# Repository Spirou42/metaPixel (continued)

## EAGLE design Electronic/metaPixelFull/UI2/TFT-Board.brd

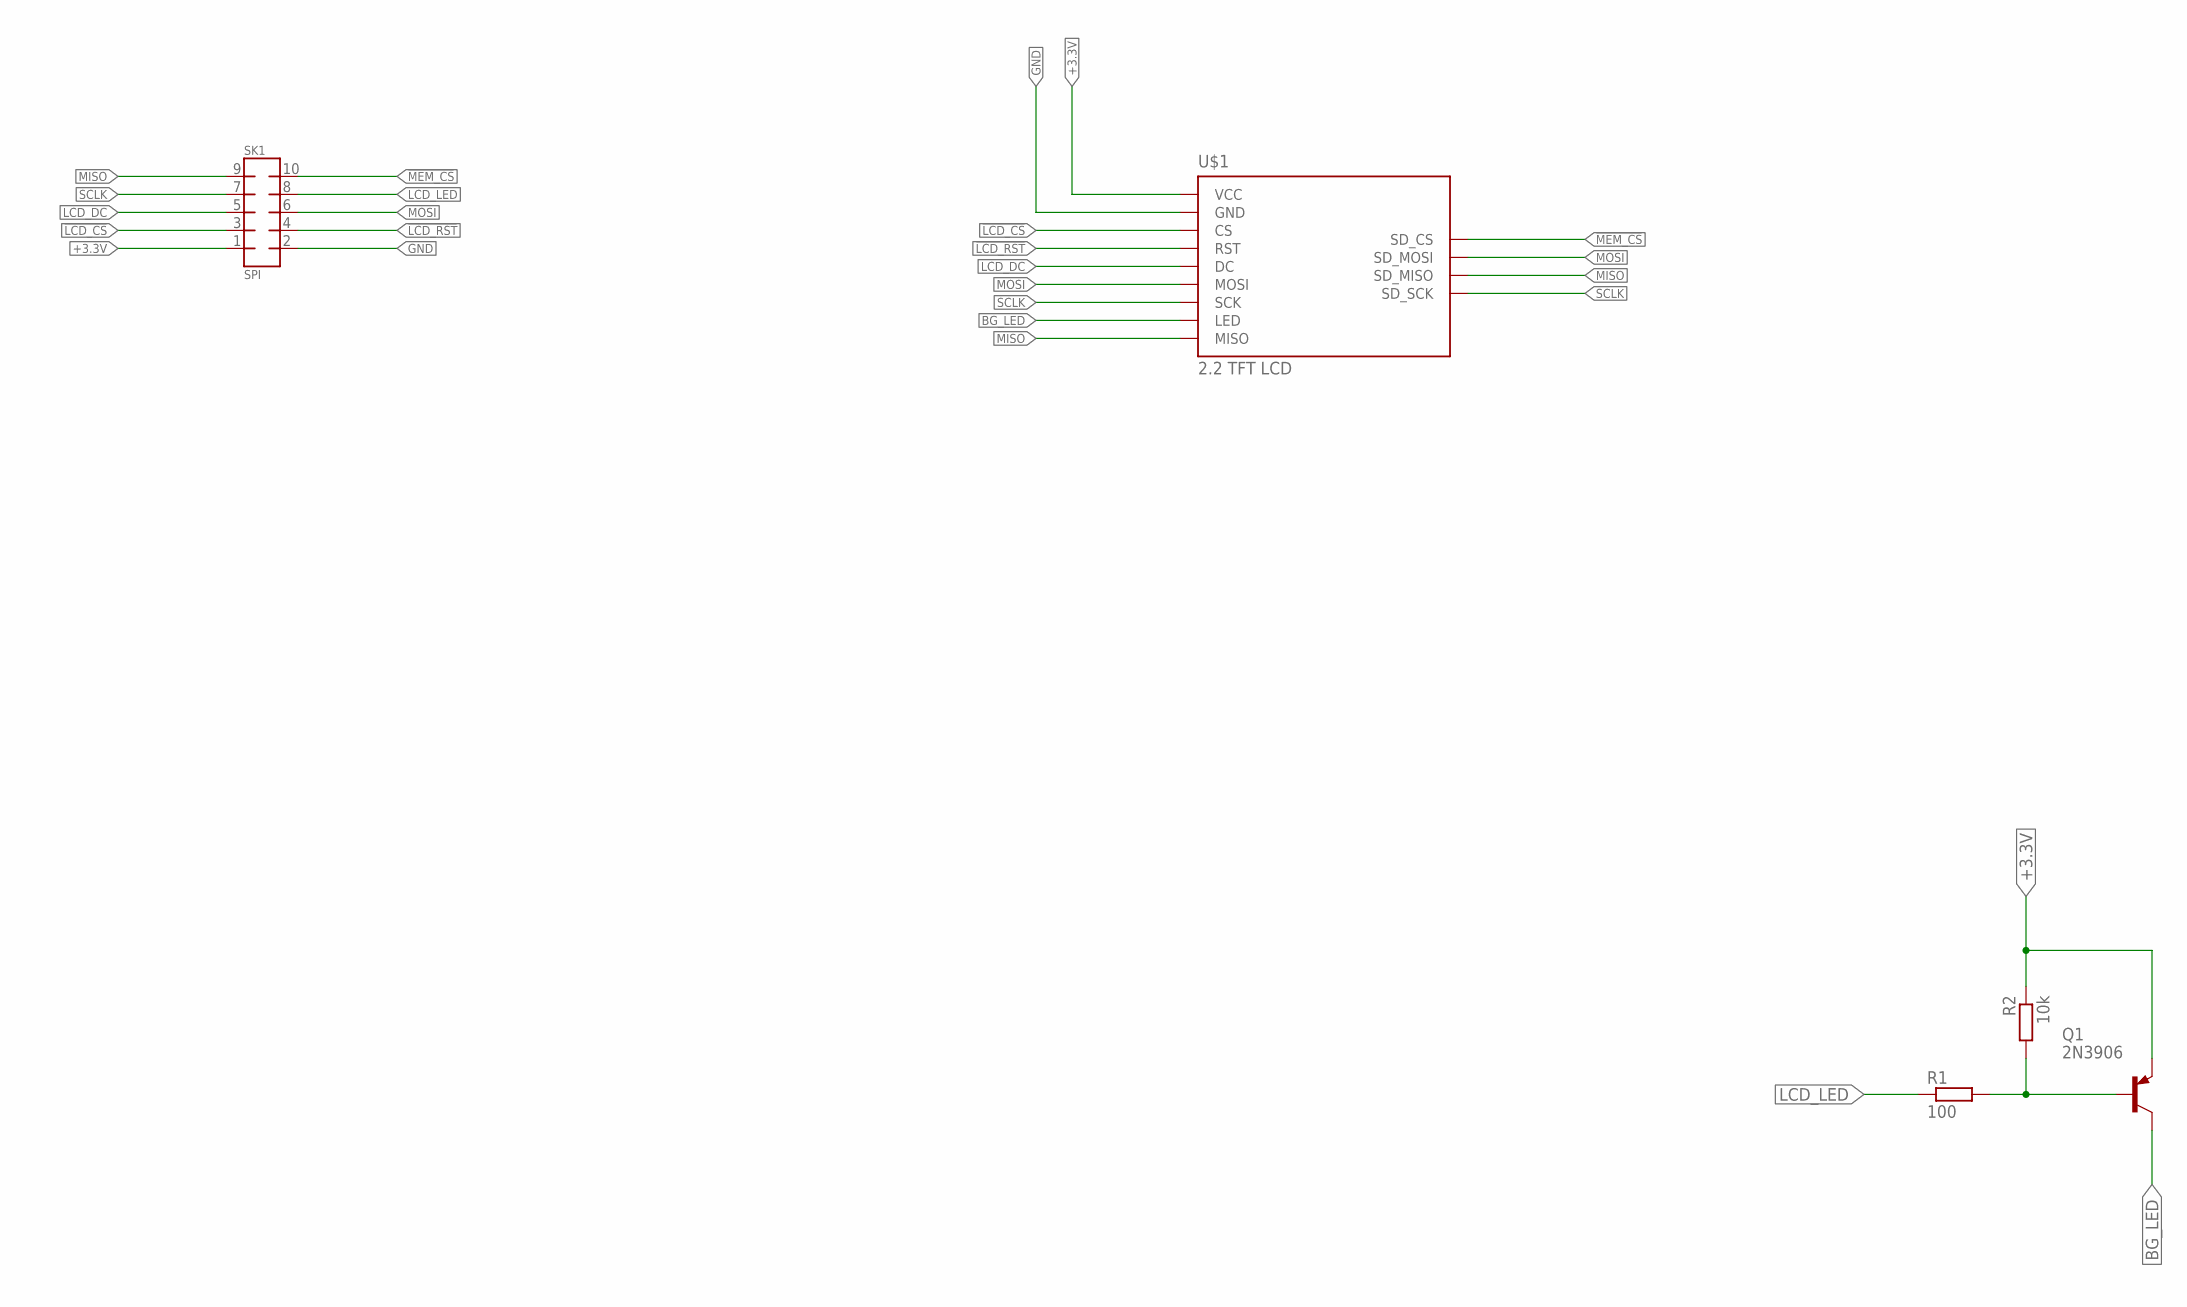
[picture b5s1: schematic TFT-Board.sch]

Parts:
Q1: 2N3906; TO92
R1: 100; 0204/7
R2: 10k; 0204/7
SK1: SPI; AMP-215079-10
U$1: 2.2_TFT_LCDNEW; 2.2_TFT_LCD_LEDSEE

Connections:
!LCD_CS: SK1.3, U$1.P$3_CS (CS)
!LCD_RST: SK1.4, U$1.P$2_RESET (RST)
!MEM_CS: SK1.10, U$1.P$2_SD_CS (SD_CS)
+3.3V: Q1.3 (E), R2.1, SK1.1, U$1.P$5_VCC (VCC)
BG_LED: Q1.1 (C), U$1.P$8_LED (LED)
GND: SK1.2, U$1.P$4_GND (GND)
LCD_DC: SK1.5, U$1.P$1_DC (DC)
LCD_LED: R1.1, SK1.8
MISO: SK1.9, U$1.P$3_SD_MISO (SD_MISO), U$1.P$9_MISO (MISO)
MOSI: SK1.6, U$1.P$1_SD_MOSI (SD_MOSI), U$1.P$6_MOSI (MOSI)
unnamed: Q1.2 (B), R1.2, R2.2
SCLK: SK1.7, U$1.P$4_SD_SCK (SD_SCK), U$1.P$7_SCK (SCK)

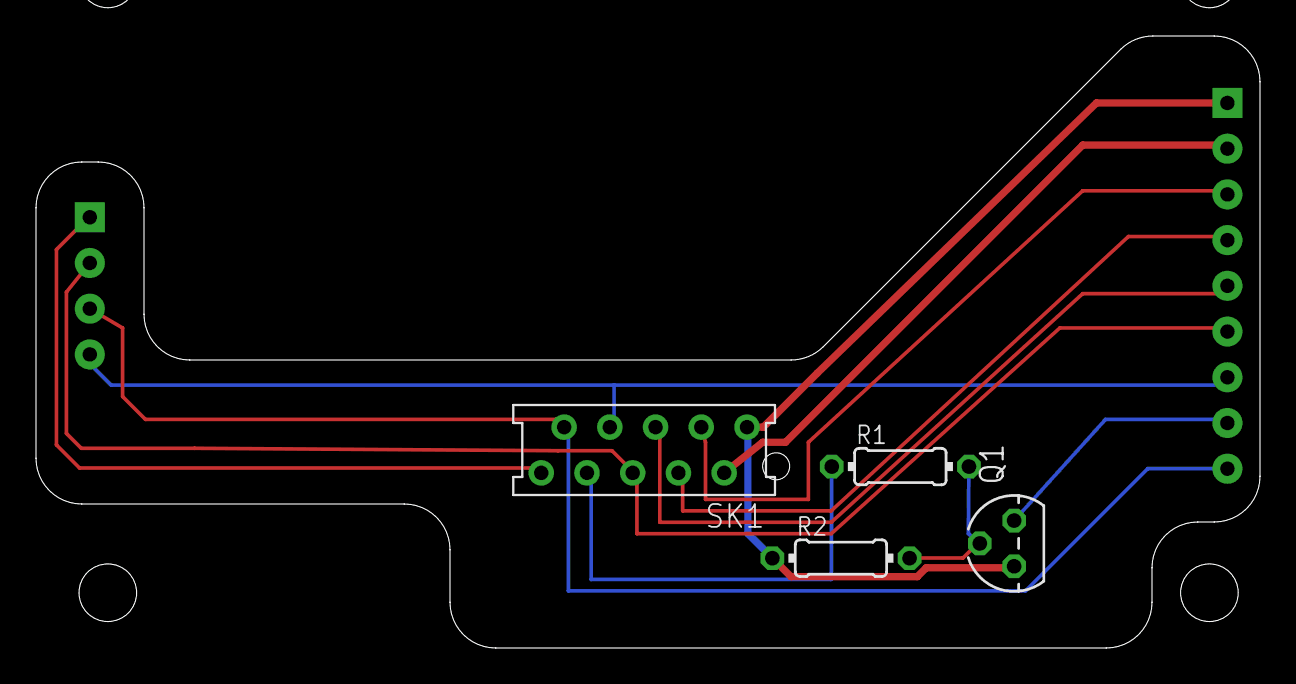
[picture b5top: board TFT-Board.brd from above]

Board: 2 copper layers, 68.0 x 34.0 mm, 5 parts (1 on the bottom side), 12 nets.

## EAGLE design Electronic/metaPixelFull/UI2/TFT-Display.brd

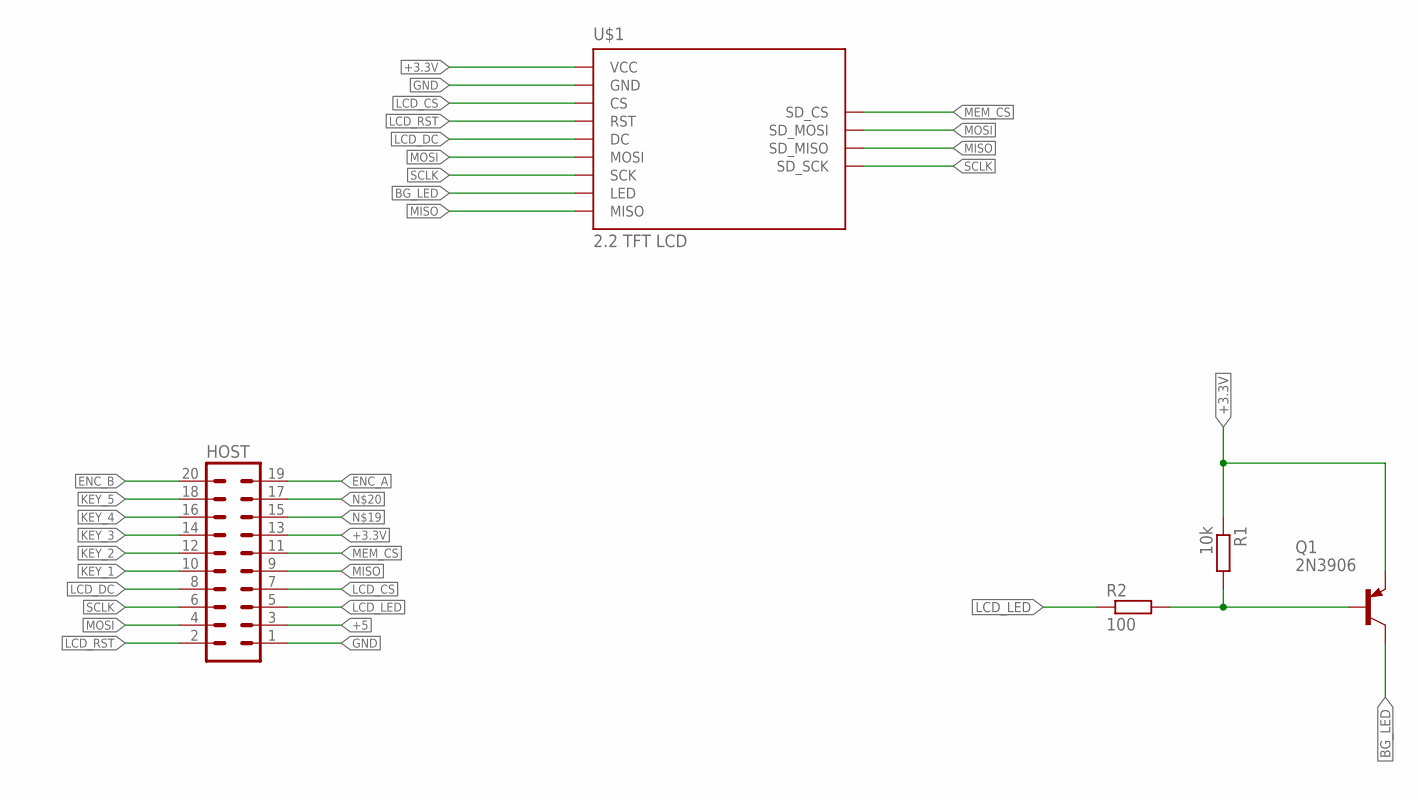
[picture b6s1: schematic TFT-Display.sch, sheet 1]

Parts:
HOST: ML20L
Q1: 2N3906; TO92
R1: 10k; 0204/7
R2: 100; 0204/7
U$1: 2.2_TFT_LCDNEW; 2.2_TFT_LCD_LEDSEE

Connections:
!LCD_CS: HOST.7, U$1.P$3_CS (CS)
!LCD_RST: HOST.2, U$1.P$2_RESET (RST)
!MEM_CS: HOST.11, U$1.P$2_SD_CS (SD_CS)
+3.3V: HOST.13, Q1.3 (E), R1.1, U$1.P$5_VCC (VCC); also elsewhere on the board
+5: HOST.3
BG_LED: Q1.1 (C), U$1.P$8_LED (LED)
ENC_A: HOST.19; also elsewhere on the board
ENC_B: HOST.20; also elsewhere on the board
GND: HOST.1, U$1.P$4_GND (GND); also elsewhere on the board
KEY_1: HOST.10; also elsewhere on the board
KEY_2: HOST.12; also elsewhere on the board
KEY_3: HOST.14; also elsewhere on the board
KEY_4: HOST.16; also elsewhere on the board
KEY_5: HOST.18; also elsewhere on the board
LCD_DC: HOST.8, U$1.P$1_DC (DC)
LCD_LED: HOST.5, R2.1
MISO: HOST.9, U$1.P$3_SD_MISO (SD_MISO), U$1.P$9_MISO (MISO)
MOSI: HOST.4, U$1.P$1_SD_MOSI (SD_MOSI), U$1.P$6_MOSI (MOSI)
unnamed: Q1.2 (B), R1.2, R2.2
SCLK: HOST.6, U$1.P$4_SD_SCK (SD_SCK), U$1.P$7_SCK (SCK)

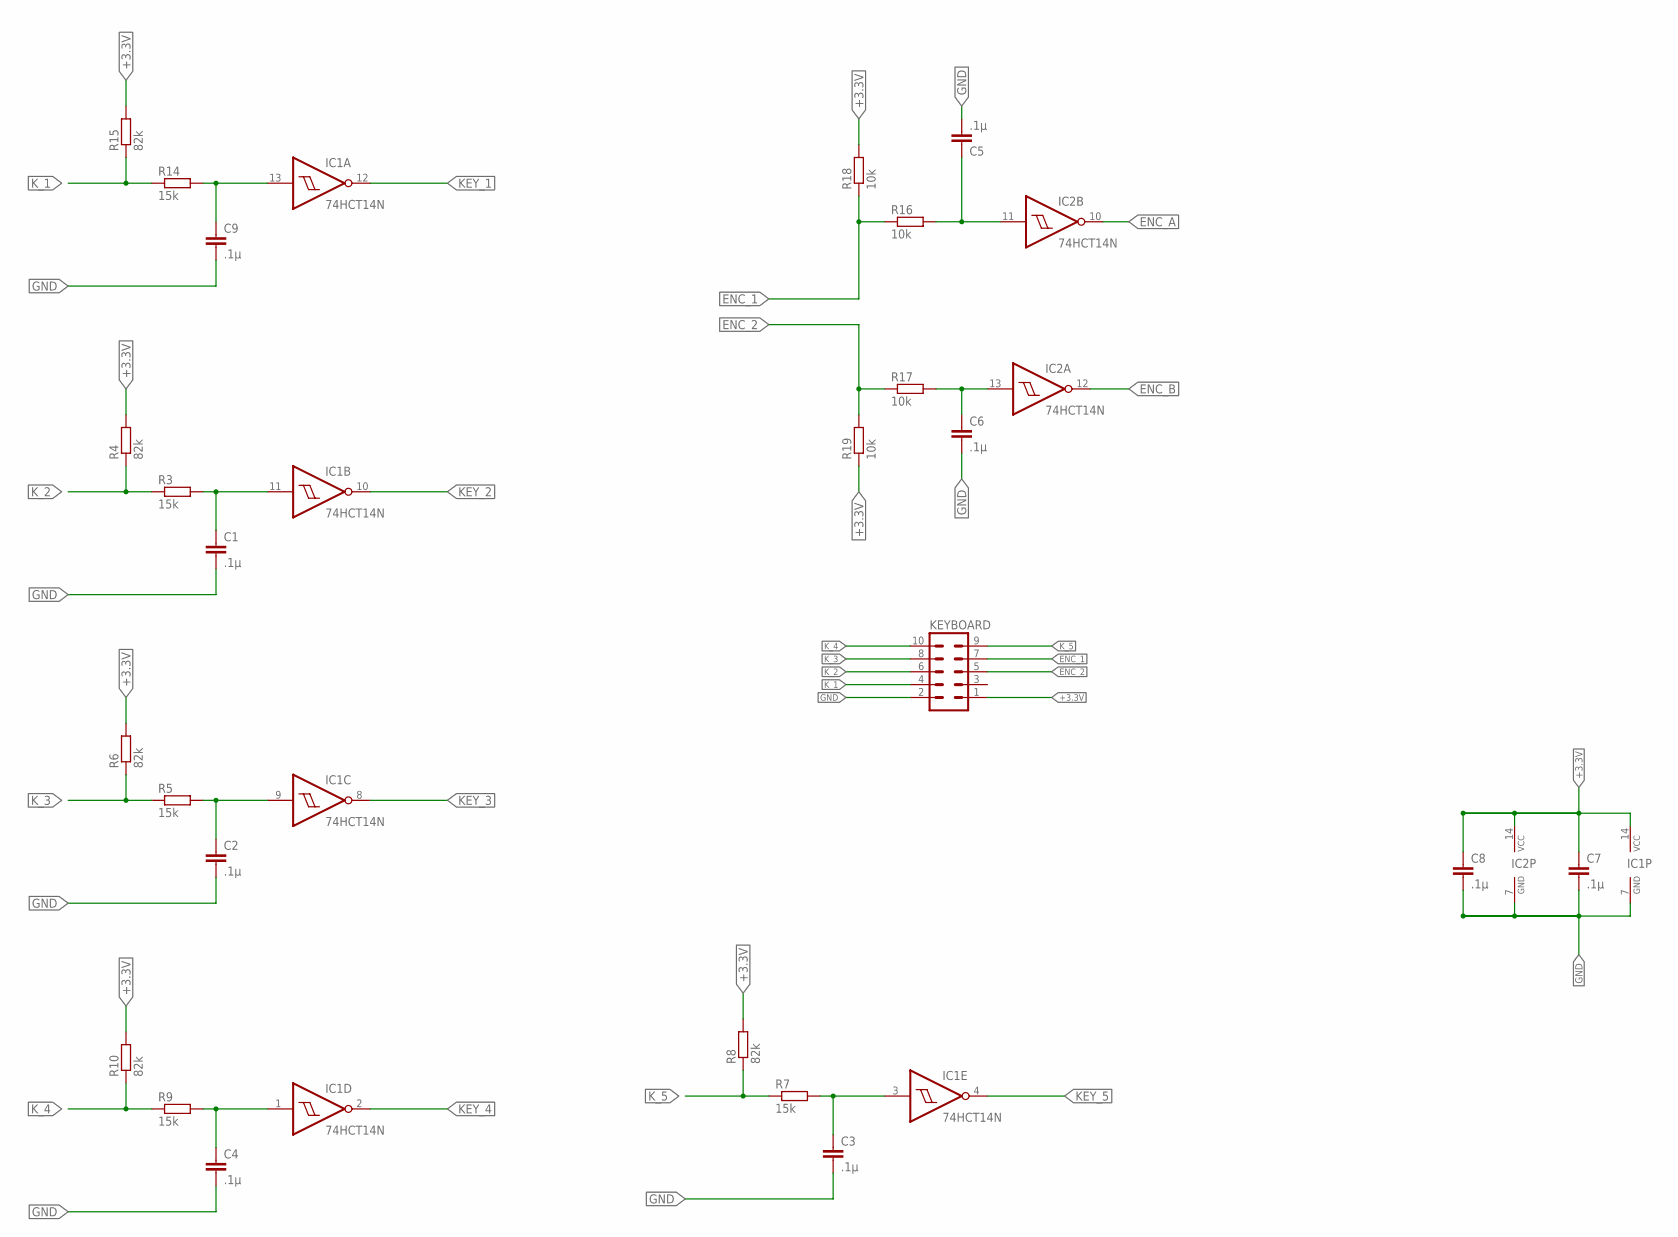
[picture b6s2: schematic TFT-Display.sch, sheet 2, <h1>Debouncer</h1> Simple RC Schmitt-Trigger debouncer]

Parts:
C1, C2, C3, C4, C5, C6, C7, C8, C9: .1µ; C025-024X044
IC1, IC2: 74HCT14N; DIL14
KEYBOARD: ML10L
R3, R5, R7, R9, R14: 15k; 0204/7
R4, R6, R8, R10, R15: 82k; 0204/7
R16, R17, R18, R19: 10k; 0204/7

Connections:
+3.3V: C7.1, C8.1, IC1.14 (VCC), IC2.14 (VCC), KEYBOARD.1, R4.2, R6.2, R8.2, R10.2, R15.2, R18.2, R19.1; also elsewhere on the board
ENC1: C5.1, IC2.11 (I), R16.2
ENC2: C6.1, IC2.13 (I), R17.2
ENC_1: KEYBOARD.7, R16.1, R18.1
ENC_2: KEYBOARD.5, R17.1, R19.2
ENC_A: IC2.10 (O); also elsewhere on the board
ENC_B: IC2.12 (O); also elsewhere on the board
GND: C1.2, C2.2, C3.2, C4.2, C5.2, C6.2, C7.2, C8.2, C9.2, IC1.7 (GND), IC2.7 (GND), KEYBOARD.2; also elsewhere on the board
K1: C9.1, IC1.13 (I), R14.2
K2: C1.1, IC1.11 (I), R3.2
K3: C2.1, IC1.9 (I), R5.2
K4: C3.1, IC1.3 (I), R7.2
K5: C4.1, IC1.1 (I), R9.2
KEY_1: IC1.12 (O); also elsewhere on the board
KEY_2: IC1.10 (O); also elsewhere on the board
KEY_3: IC1.8 (O); also elsewhere on the board
KEY_4: IC1.2 (O); also elsewhere on the board
KEY_5: IC1.4 (O); also elsewhere on the board
K_1: KEYBOARD.4, R14.1, R15.1
K_2: KEYBOARD.6, R3.1, R4.1
K_3: KEYBOARD.8, R5.1, R6.1
K_4: KEYBOARD.10, R9.1, R10.1
K_5: KEYBOARD.9, R7.1, R8.1

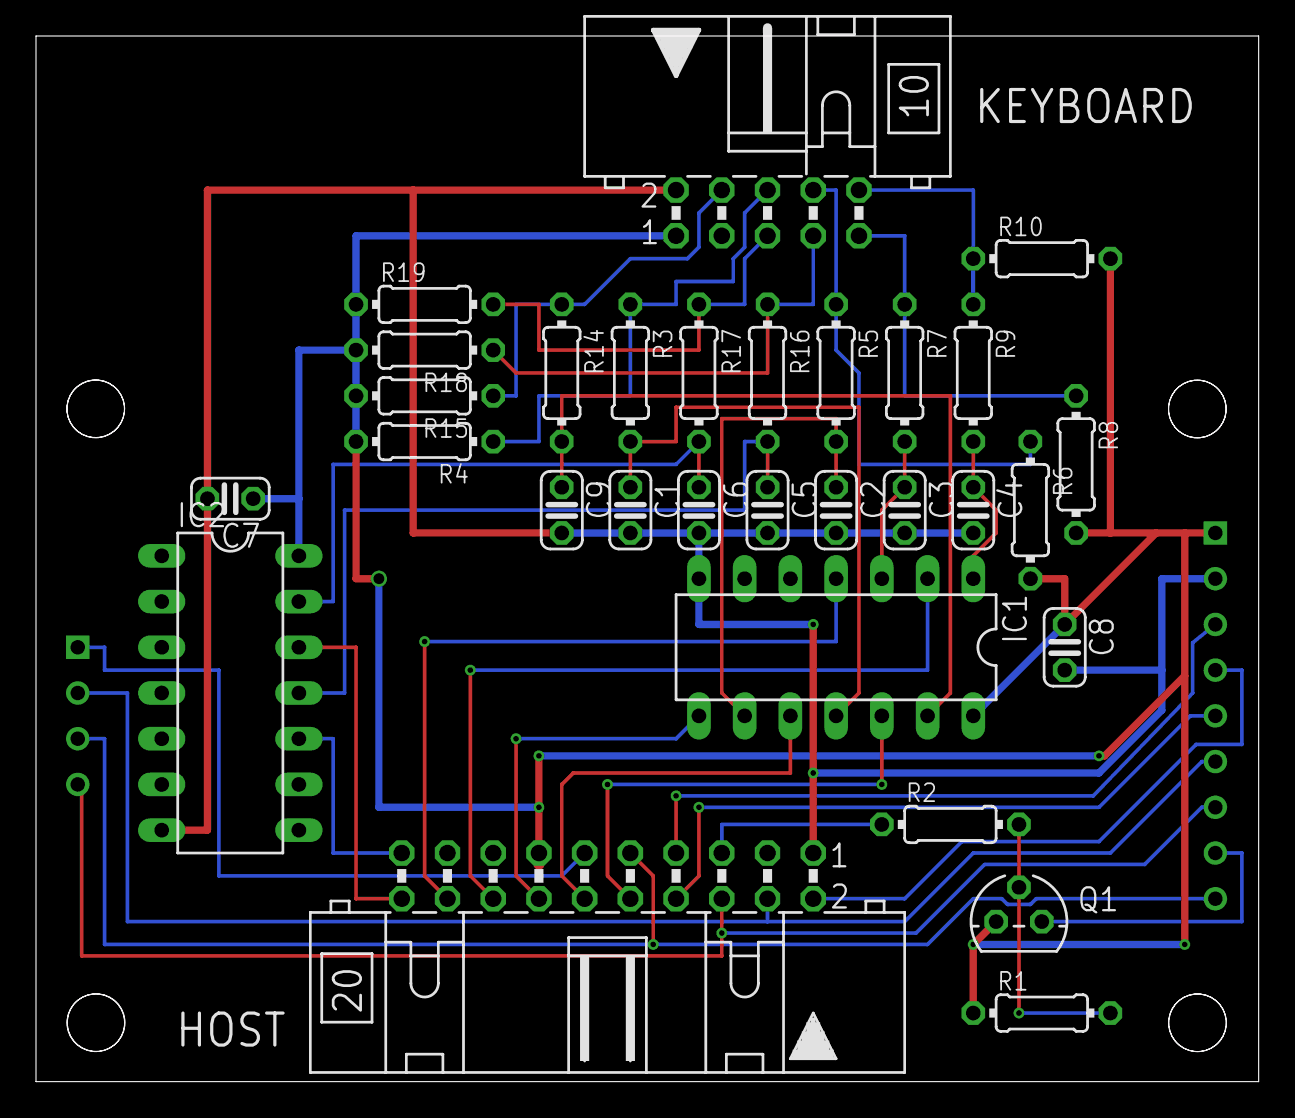
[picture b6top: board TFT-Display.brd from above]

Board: 2 copper layers, 67.9 x 58.1 mm, 31 parts (1 on the bottom side), 33 nets.

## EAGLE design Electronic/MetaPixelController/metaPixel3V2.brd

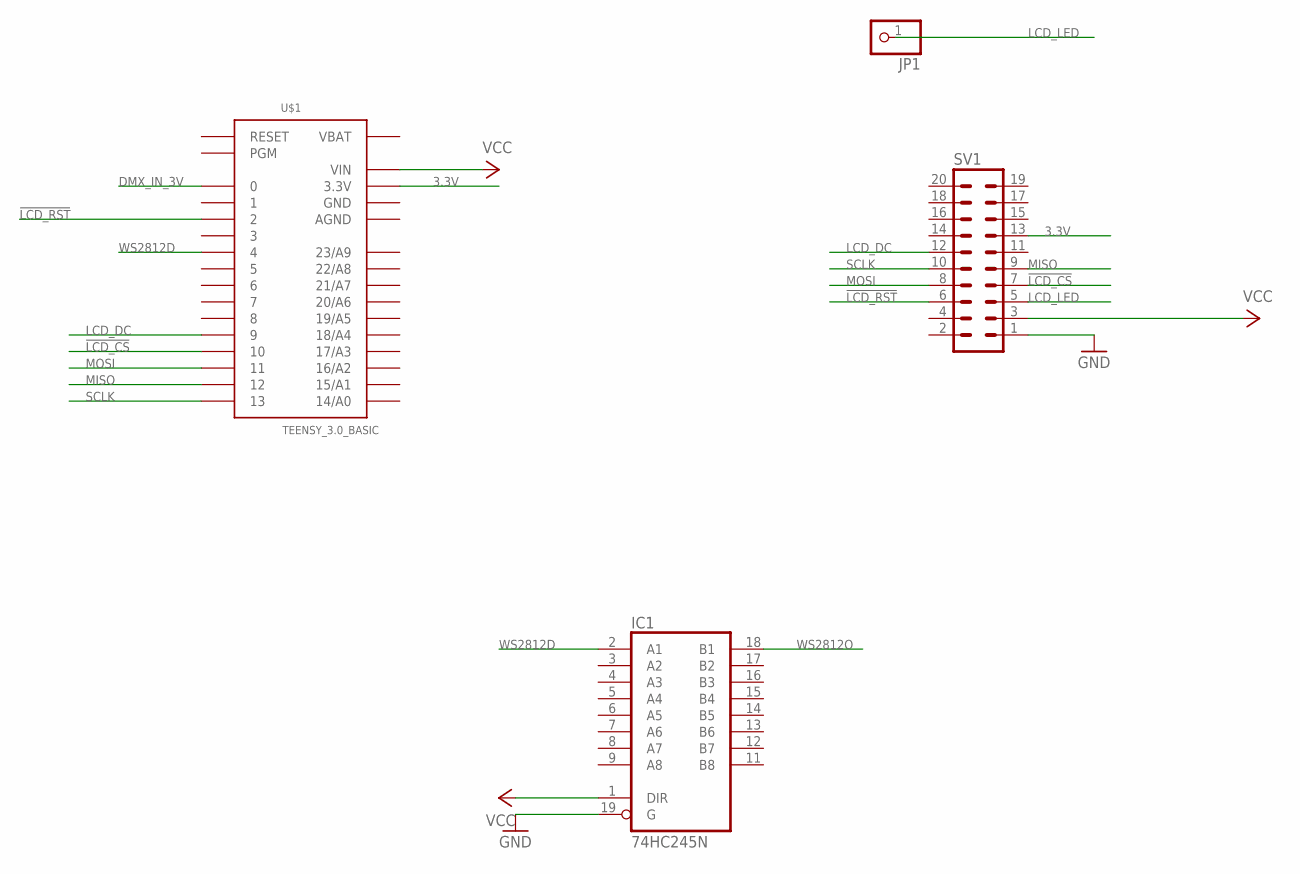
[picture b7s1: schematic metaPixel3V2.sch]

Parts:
IC1: 74HC245N; DIL20
JP1: PINHD-1X1; 1X01
SV1: ML20
U$1: TEENSY_3.0_BASIC

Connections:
3.3V: SV1.13, U$1.3.3V, U$1.3.3V1 (3.3V)
!LCD_CS: SV1.7, U$1.10
!LCD_RST: SV1.6, U$1.2
AGND: U$1.AGND
DMX_IN_3V: U$1.0
GND: IC1.10 (GND), IC1.19 (G), SV1.1, U$1.GND, U$1.GND1 (GND)
LCD_DC: SV1.12, U$1.9
LCD_LED: JP1.1, SV1.5
MISO: SV1.9, U$1.12
MOSI: SV1.8, U$1.11
SCLK: SV1.10, U$1.13
VBAT: U$1.VBAT
VCC: IC1.1 (DIR), IC1.20 (VCC), SV1.3, U$1.VIN
WS2812D: IC1.2 (A1), U$1.4
WS2812O: IC1.18 (B1)

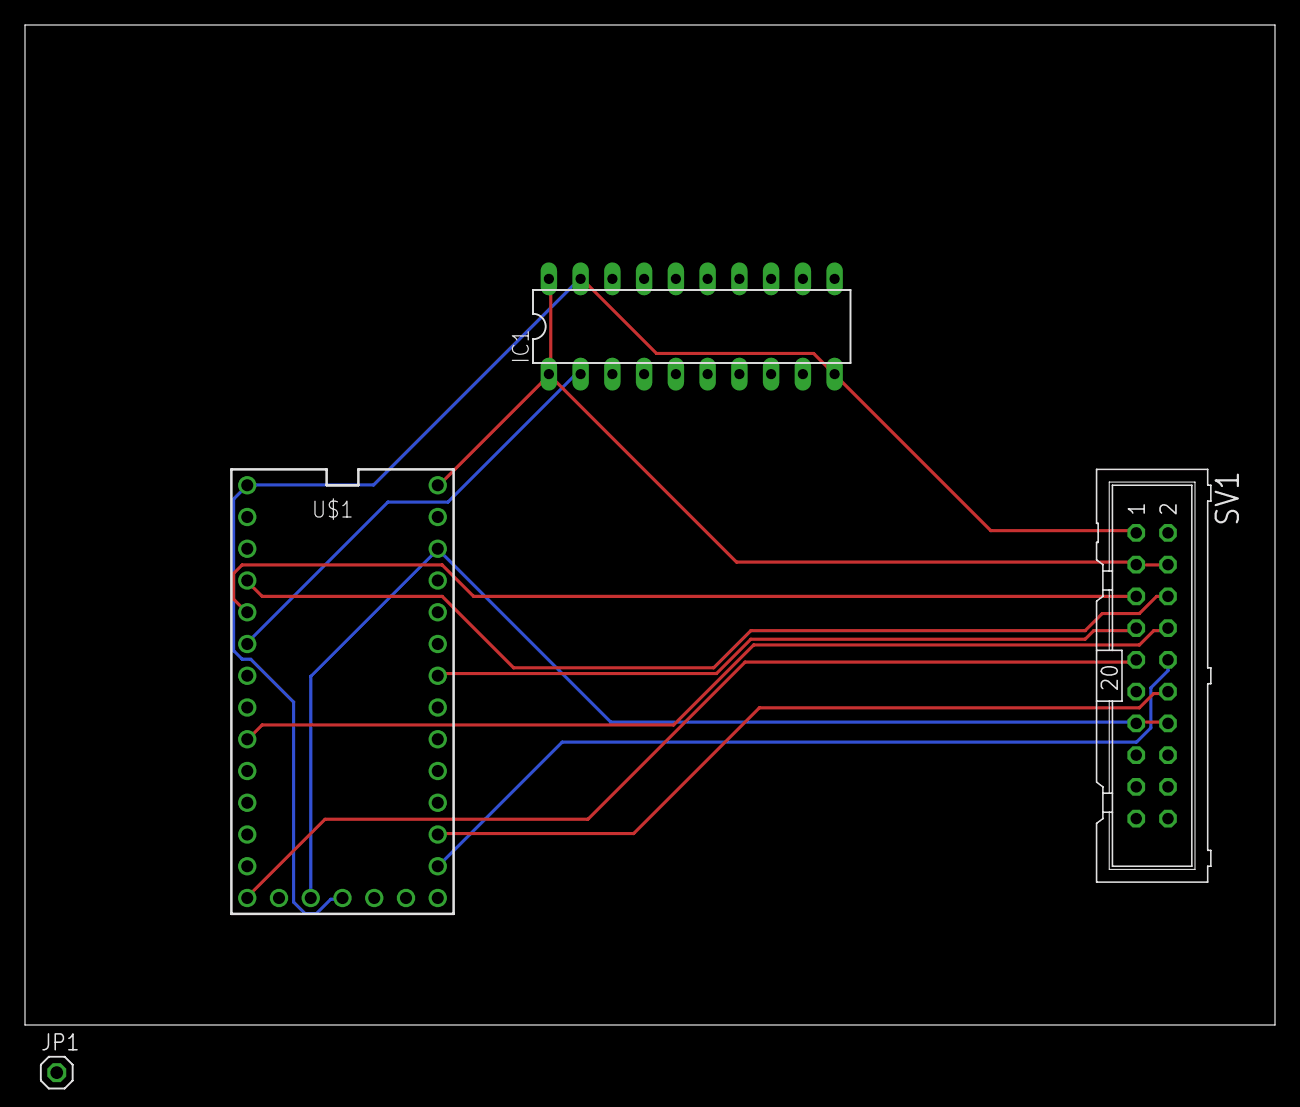
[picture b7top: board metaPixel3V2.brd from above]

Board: 2 copper layers, 100.0 x 80.0 mm, 4 parts (0 on the bottom side), 11 nets.

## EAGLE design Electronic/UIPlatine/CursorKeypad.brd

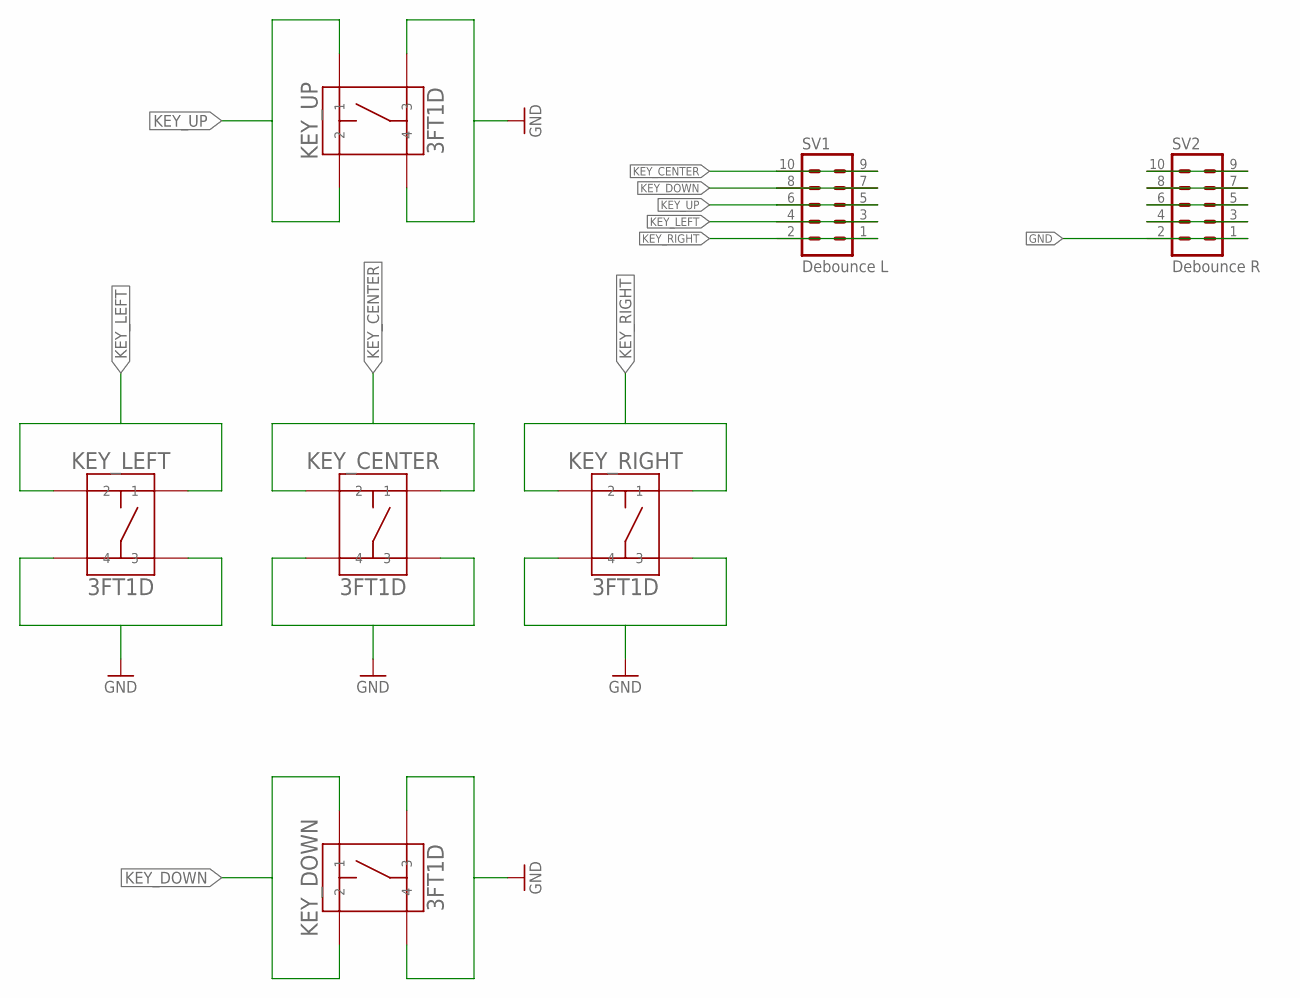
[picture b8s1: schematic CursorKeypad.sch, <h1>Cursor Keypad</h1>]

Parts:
KEY_CENTER: 3FT1D; 3FT
KEY_DOWN: 3FT1D; 3FT
KEY_LEFT: 3FT1D; 3FT
KEY_RIGHT: 3FT1D; 3FT
KEY_UP: 3FT1D; 3FT
SV1: Debounce L; MA05-2
SV2: Debounce R; MA05-2

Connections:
GND: KEY_CENTER.P$3 (3), KEY_CENTER.P$4 (4), KEY_DOWN.P$3 (3), KEY_DOWN.P$4 (4), KEY_LEFT.P$3 (3), KEY_LEFT.P$4 (4), KEY_RIGHT.P$3 (3), KEY_RIGHT.P$4 (4), KEY_UP.P$3 (3), KEY_UP.P$4 (4), SV2.1, SV2.2
KEY_CENTER: KEY_CENTER.P$1 (1), KEY_CENTER.P$2 (2), SV1.9, SV1.10
KEY_DOWN: KEY_DOWN.P$1 (1), KEY_DOWN.P$2 (2), SV1.7, SV1.8
KEY_LEFT: KEY_LEFT.P$1 (1), KEY_LEFT.P$2 (2), SV1.3, SV1.4
KEY_RIGHT: KEY_RIGHT.P$1 (1), KEY_RIGHT.P$2 (2), SV1.1, SV1.2
KEY_UP: KEY_UP.P$1 (1), KEY_UP.P$2 (2), SV1.5, SV1.6
unnamed: SV2.9, SV2.10
unnamed: SV2.7, SV2.8
unnamed: SV2.5, SV2.6
unnamed: SV2.3, SV2.4

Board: 2 copper layers, 7 parts (3 on the bottom side), 10 nets, no tracks yet.

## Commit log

2015-08-07 initial commit
    of all the stuff done till now
2015-08-09 BlaBla
2015-08-10 new values
2015-08-10 Sharing parameters between noise and plasma
2015-08-10 another parameter shared
2015-08-11 main controller board layout with DMX client only
2015-08-11 eagle project changes
2015-08-11 tweaking Effects
2015-08-11 Ready update
2015-08-11 come on baby, light my fire
2015-08-13 more fancy stuff
2015-08-14 ongoing restructuring of the whole effect/parameter handling
2015-08-14 Next generation
2015-08-17 and another change in the eagle epf - strange
2015-08-17 ignoring sheet files
2015-08-17 procrastinating - minor changes to the Audio version -
2015-08-17 elf again ???
2015-08-18 new effect/parameter structure up and running
    All effects use the new parameter and effect structure
    Menu and Encoder UI disabled
    Teensy Audio shield compatibility
2015-08-18 why was this file not in the last commit?
2015-08-19 further reworking of old structures
2015-08-19 removing legacy effect
2015-08-19 Waterfall display
2015-08-20 Audio switchable
2015-08-20 renaming
2015-08-22 another great step
    - animated Parameter
    - VT100 escapes on Serial
2015-08-22 fixed parameter animation for target<current
2015-08-22 update of Command line interface
2015-08-22 animated Parameter
    bounce and animate from the command line
2015-08-24 Removing a couple of eagle files
2015-08-28 more cowbell
2015-08-28 Images, Readme, stuff
2015-08-28 Command Class
    simple implementation of a simple command class.
2015-08-29 better command processor
    value change and animation commands are now encapsulated into a
    commandObject and placed in a command queue which is processed in the
    main run loop.
2015-08-29 fixing parser problem
    adding shaped mirror mode
2015-08-29 tweak command parser
    added instant command execution path for programatically initiated
    commands
2015-08-29 sparkle as a parameter for the fire effect
2015-09-01 command rework
    removed all command parser
    added parameter names to effects
    added more beautiful VT100 output
2015-09-02 fixin parameter output
2015-10-12 some rework
2015-10-13 Renaming and a new file
2015-10-14 WaitForAnimation
    - removing dependency to TeensyAudio
2015-10-15 Some smaller reworks
2015-10-15 Docu
2015-10-15 added documentation
2015-10-16 tweaking Command processor and adding sequence code
2015-10-16 comments
2015-10-16 effect program presets
    changed command mnemonics
2015-10-17 added Documentation for the 2.2" ledsee tat display
2015-10-18 Stuff
    resolution switch for display
    renaming of globals
    output of parameter settings adapts automatically to new parameters
2015-10-20 Added an ILI9341 Display
2015-10-20 removing Audio Configuration
    moving SPI to default for ILI
    removing legacy stuff.
    moving to current ILI lib
2015-10-21 fixing include stuff
2015-10-22 Planing a new UI Board
2015-10-22 new UI
2015-10-23 planing a new UI concept
2015-10-25 Updated connectors
    and more work on the UI Boards
2015-10-28 adding a new CursorCross for EC60A/B usage
2015-10-29 new Keycross and EC60A board
2015-10-29 Removing the obsolete test code
    which was provided by the Chinese source
2015-10-29 board positions
2015-10-29 Hurga
2015-10-30 Boardwork
2015-10-30 removing a couple of unused libs
2015-10-30 removing some files
2015-10-30 Building the UI-Board
2015-10-30 Display board layout
2015-11-03 The first 3 Boards are ready
2015-11-04 the mainboard
2015-11-04 Layout 1
2015-11-05 boards
2015-11-06 adding another .log to the ignore file
2015-11-10 minor changes
2015-11-19 adding a couple of data sheets
2015-11-22 Reworking the Controller
2015-11-23 Adding Lumberer datasheets
2015-11-23 adding lumberger library
2015-11-26 no lock files
2015-11-26 removing legacy file
2015-11-26 Adding TFT UI development project
2015-11-26 Creating UI helpers
2015-11-27 std::vector up and running
2015-11-28 working on the UI
    creating helper classes and a simple view structure
2015-11-29 Fixing analog backlightproblem
    creating a couple of view helper classes.
    adding Display brightens control.
2015-11-29 removing outside dependencies from Parameter.h
2015-11-29 creating a demo real for the TFT
2015-11-29 argl
2015-11-30 doing the effect twist
2015-11-30 Bäh geht nicht
2015-11-30 Where are the Fonts.
2015-11-30 one step further
    adding auto layout methods like sizetoFit .
2015-12-03 another brick in the wall
2015-12-03 switching LED pin
2015-12-03 money for nothing
2015-12-04 Select state
2015-12-05 list auto layout
    Select states and more layout options for views and labels.
2015-12-06 Better, everything gets better
2015-12-06 up and away
2015-12-07 Naming Parameters
2015-12-07 metaValue is back again
2015-12-08 value display
2015-12-09 switching views and actions
2015-12-09 Actions up and running
2015-12-10 working parameters and menus
2015-12-10 Humpe
2015-12-10 encoder acceleration
2016-01-27 Double LED ring
2016-01-27 Removing the TFT from the Debouncer
2016-02-09 Restructure Hardware
    prepare for an TFT only adapter board
2016-02-09 Scrollable lists
    First simple version with scrollable lists.
    - some clean up has to be done.
    - visual representation for IN LIST position is missing
2016-02-11 small changes to effects
2016-02-16 Blafa
2016-02-16 fixed
2016-03-01 schnack
2016-03-07 rework UI
2016-03-11 Sülzfleisch in Tüten
2016-03-13 Fixing the boards
2016-03-13 final CAM result
2016-03-14 fixing size issue
2016-03-14 Baaaaaaaaaaaaal
2016-03-31 fixing TFT_LED problem
2016-04-04 macros and finishing
2016-04-05 switches now work
2016-04-05 Tweaking Effects
    - adding macro start on power on
    - endless demo Macro and tweaked animation.
2016-04-09 removing unused boards and files
2016-04-09 renaming an STL and adding a bunch of CAD files
2016-04-09 How the hack have i created this stuff?
2016-04-09 removing the EffectsCollection - no inspiration need any more
2016-04-09 removing unused software components.
    There will be no TFT UI for metaPixel display in the actual version.
    metaTFT will be republished after renaming and rework of the UI
    elements.
2016-04-10 tweaking frame rate and adding water effect
2016-04-13 renaming effect and creating water 1
2016-04-16 Beautiful water
2016-09-06 Renaming some some header files
2016-09-07 adding info to the documentation
2017-08-03 renaming galore
2017-12-14 added some warning if module dimensions are not set
2018-01-23 minor changes to the Readme
